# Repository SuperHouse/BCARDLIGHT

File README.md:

Jon's SuperHouse Business Card
===============================
Copyright 2015 SuperHouse Automation Pty Ltd  www.superhouse.tv  

A business card designed as a PCB, with parts to make a datalogger
based on a TEMT6000 light sensor and an ATtiny85.

Features:

 * Micro USB header
 * ATtiny85 MCU
 * TEMT6000 light sensor

INSTALLATION
------------
The design is saved as an EAGLE project. EAGLE PCB design software is
available from www.cadsoftusa.com free for non-commercial use. To use
this project download it and place the directory containing these files
into the "eagle" directory on your computer. Then open EAGLE and
navigate to the project.

CREDITS
-------
Designed by Jonathan Oxer jon@oxer.com.au  

DISTRIBUTION
------------
The specific terms of distribution of this project are governed by the
license referenced below.

LICENSE
-------
Licensed under the TAPR Open Hardware License (www.tapr.org/OHL).
The "license" folder within this repository also contains a copy of
this license in plain text format.

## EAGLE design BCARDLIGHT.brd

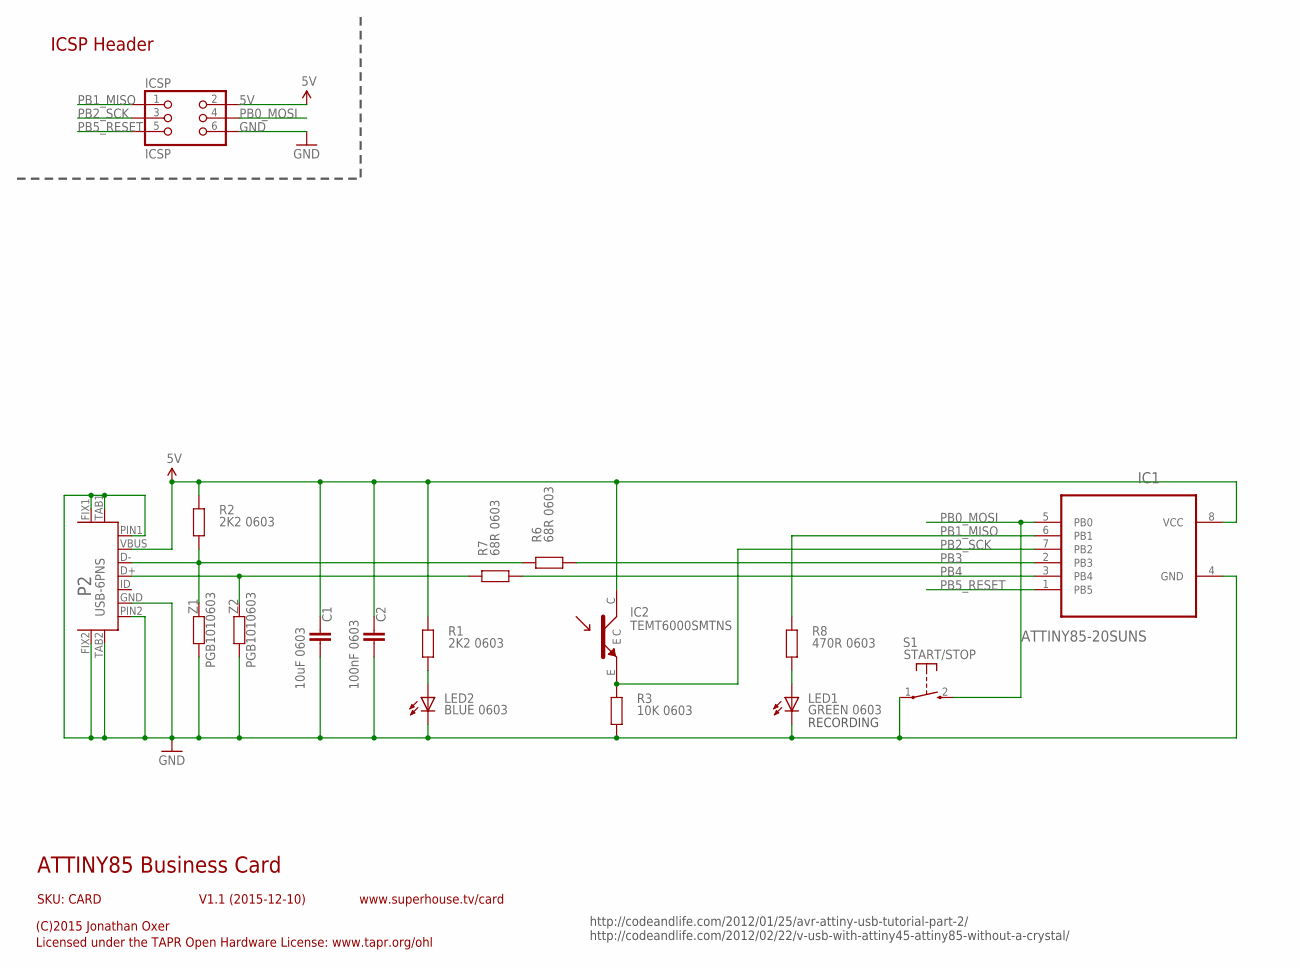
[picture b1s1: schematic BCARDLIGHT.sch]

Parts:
C1: 10uF 0603; 0603_NO_SILK
C2: 100nF 0603; 0603_NO_SILK
IC1: ATTINY85-20SUNS; SOIC127P798X216-8N_NO_SILK
IC2: TEMT6000SMTNS; TEMT6000_NO_SILK
ICSP: ICSP; 2X03SURFACE_NO_SILK
LED1: GREEN 0603; 0603_NO_SILK
LED2: BLUE 0603; 0603_NO_SILK
P2: USB-6PNS; USB-MICROB-MB05PMXX_NO_SILK
R1, R2: 2K2 0603; 0603_NO_SILK
R3: 10K 0603; 0603_NO_SILK
R6, R7: 68R 0603; 0603_NO_SILK
R8: 470R 0603; 0603_NO_SILK
S1: START/STOP; TACTILE_SWITCH_SMD_2PIN_TINY_NO_SILK
Z1, Z2: PGB1010603; 0603_NO_SILK

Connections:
5V: C1.1, C2.1, IC1.8 (VCC), IC2.C, ICSP.2, P2.VBUS, R1.2, R2.2
D+: P2.D+, R7.2, Z2.2
D-: P2.D-, R2.1, R6.2, Z1.2
GND: C1.2, C2.2, IC1.4 (GND), ICSP.6, LED1.2 (C), LED2.2 (C), P2.FIX1, P2.FIX2, P2.GND, P2.PIN1, P2.PIN2, P2.TAB1, P2.TAB2, R3.1, S1.1, Z1.1, Z2.1
unnamed: LED2.1 (A), R1.1
unnamed: LED1.1 (A), R8.1
PB0_MOSI: IC1.5 (PB0), ICSP.4, S1.2 (S)
PB1_MISO: IC1.6 (PB1), ICSP.1, R8.2
PB2_SCK: IC1.7 (PB2), IC2.E, ICSP.3, R3.2
PB3: IC1.2 (PB3), R6.1
PB4: IC1.3 (PB4), R7.1
PB5_RESET: IC1.1 (PB5), ICSP.5

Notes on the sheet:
ICSP Header
ATTINY85 Business Card
V1.1 (2015-12-10)
SKU: CARD
(C)2015 Jonathan Oxer
Licensed under the TAPR Open Hardware License: www.tapr.org/ohl
www.superhouse.tv/card
http://codeandlife.com/2012/01/25/avr-attiny-usb-tutorial-part-2/ http://codeandlife.com/2012/02/22/v-usb-with-attiny45-attiny85-without-a-crystal/
RECORDING

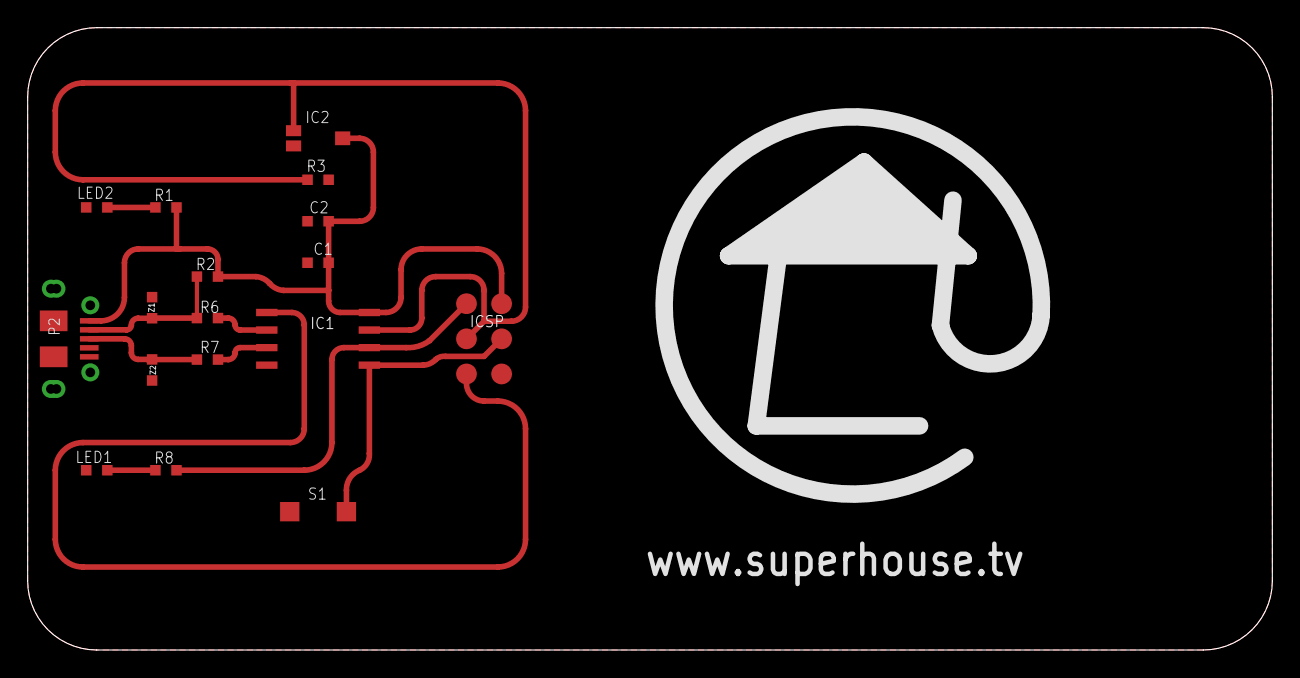
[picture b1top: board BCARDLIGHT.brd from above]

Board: 2 copper layers, 90.0 x 45.0 mm, 17 parts (0 on the bottom side), 12 nets.

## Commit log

2018-03-23 Initial project import
